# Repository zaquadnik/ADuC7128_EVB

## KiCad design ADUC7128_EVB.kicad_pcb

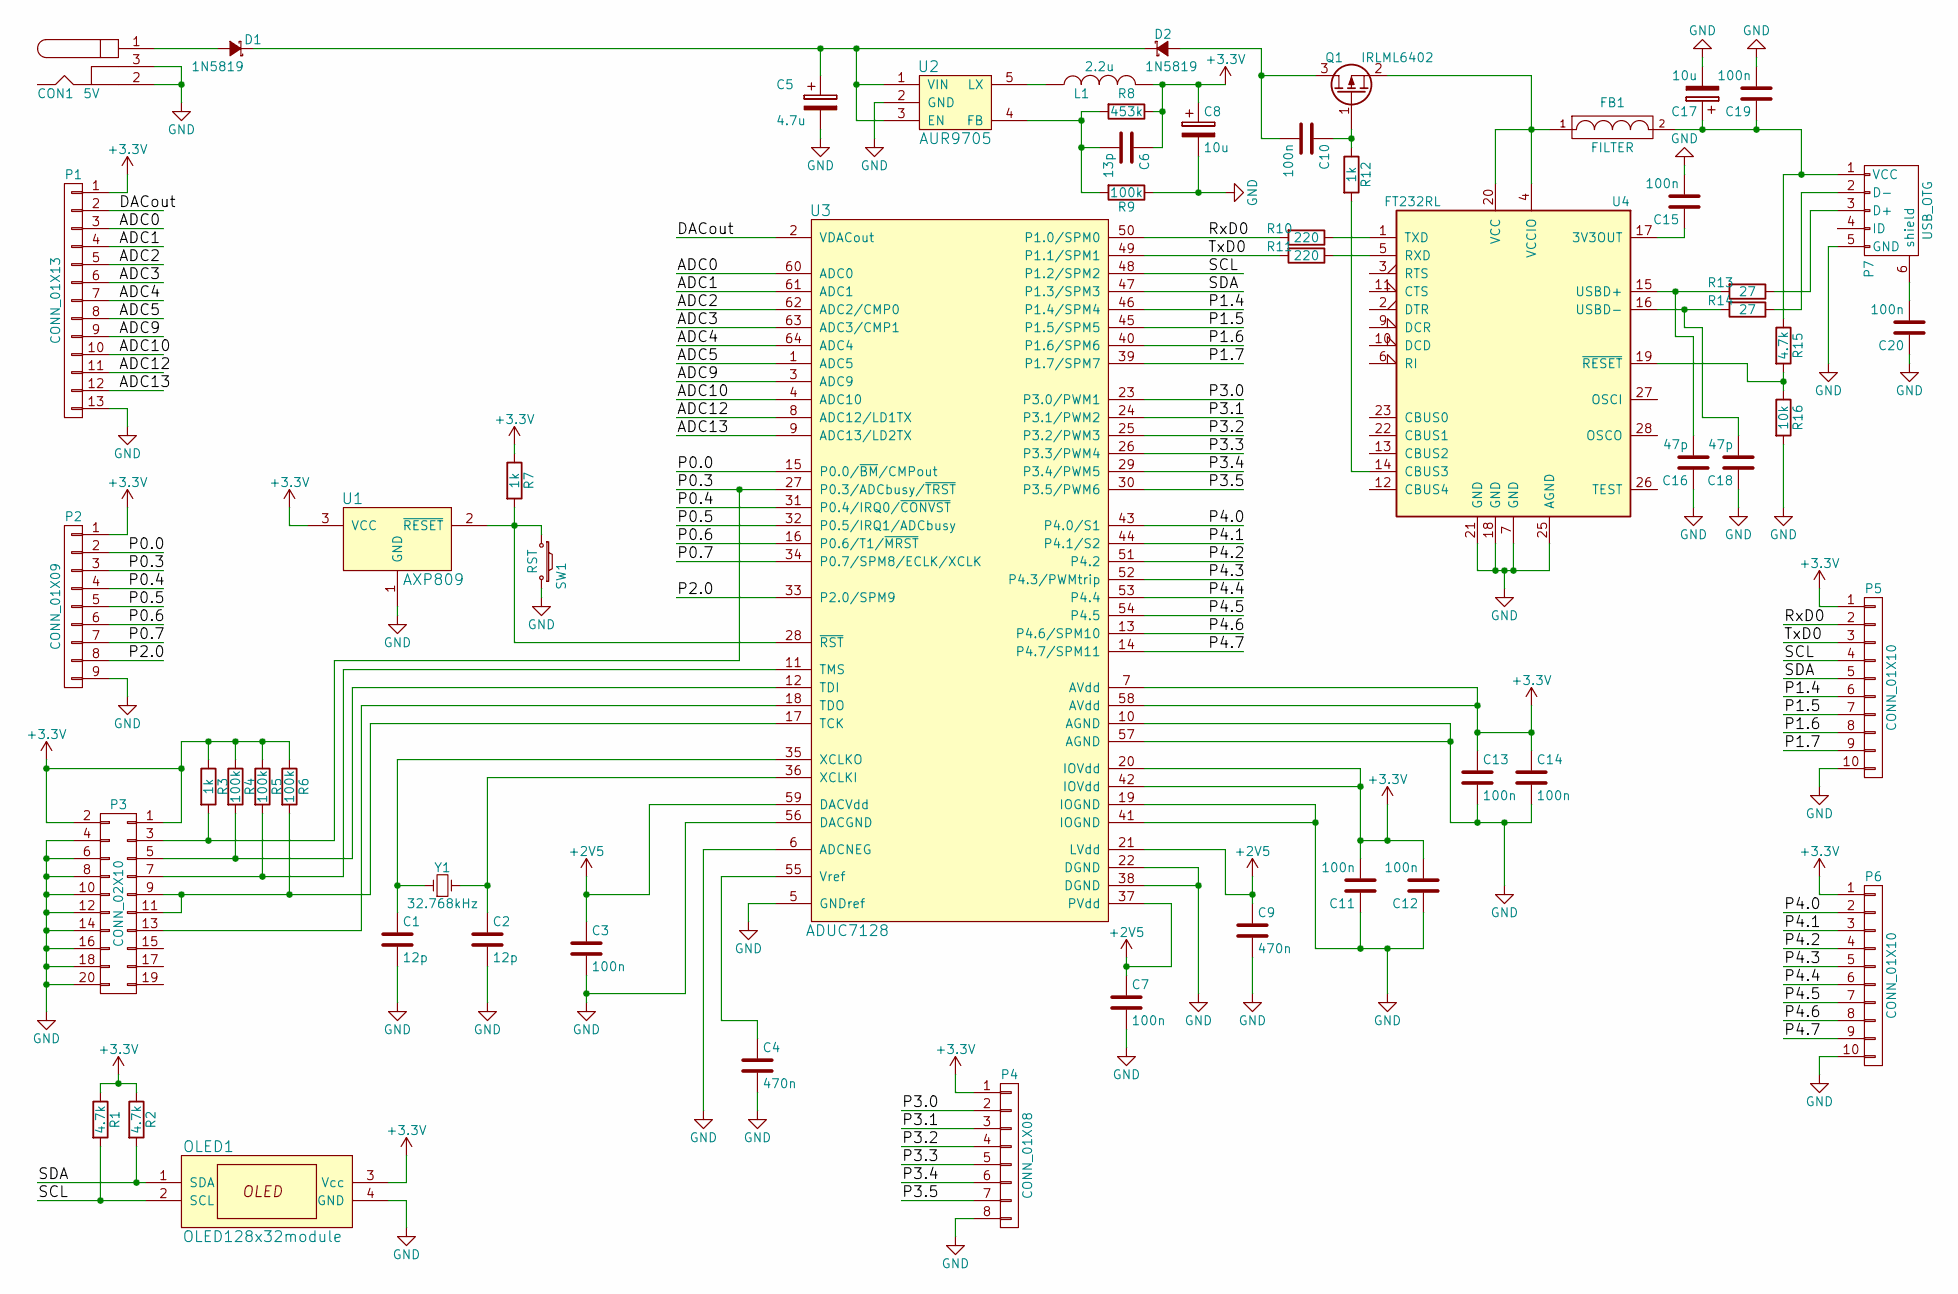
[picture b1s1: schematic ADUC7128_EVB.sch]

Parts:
C1, C2: 12p; C_0805_HandSoldering
C3, C7, C10, C11, C12, C13, C14, C15, C19, C20: 100n; C_0805_HandSoldering
C4, C9: 470n; C_0805_HandSoldering
C5: 4.7u; CP_Radial_D5.0mm_P2.00mm
C6: 13p; C_0805_HandSoldering
C8, C17: 10u; CP_Radial_D5.0mm_P2.50mm
C16, C18: 47p; C_0805_HandSoldering
CON1: 5V; BARREL_JACK
D1, D2: 1N5819; D_DO-41_SOD81_P7.62mm_Horizontal
FB1: FILTER; Choke_SMD_1206_Handsoldering
L1: 2.2u; Inductor_Taiyo-Yuden_NR-30xx_HandSoldering
OLED1: OLED128x32module; OLED_128x32_module
P1: CONN_01X13; Pin_Header_Straight_1x13_Pitch2.54mm
P2: CONN_01X09; Pin_Header_Straight_1x09_Pitch2.54mm
P3: CONN_02X10; Pin_Header_Straight_2x10_Pitch2.54mm
P4: CONN_01X08; Pin_Header_Straight_1x08_Pitch2.54mm
P5, P6: CONN_01X10; Pin_Header_Straight_1x10_Pitch2.54mm
P7: USB_OTG; USB_Mini-B
Q1: IRLML6402; SOT-23W_Handsoldering
R1, R2, R15: 4.7k; R_0603_HandSoldering
R3, R7, R12: 1k; R_0603_HandSoldering
R4, R5, R6, R9: 100k; R_0603_HandSoldering
R8: 453k; R_0603_HandSoldering
R10, R11: 220; R_0603_HandSoldering
R13, R14: 27; R_0603_HandSoldering
R16: 10k; R_0603_HandSoldering
SW1: RST; SW_PUSH_6mm
U1: AXP809; SC-59_Handsoldering
U2: AUR9705; TSOT-23-5_HandSoldering
U3: ADUC7128; QFP_64
U4: FT232RL; SSOP-28_5.3x10.2mm_Pitch0.65mm
Y1: 32.768kHz; Crystal_AT310_d3.0mm_l10.0mm_Vertical

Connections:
+2V5: C3.1, C7.1, C9.1, U3.21 (LVdd), U3.37 (PVdd), U3.59 (DACVdd)
+3V3: C6.1, C8.1, C11.2, C12.2, C13.1, C14.1, L1.2, OLED1.3 (Vcc), P1.1, P2.1, P3.1, P3.2, P4.1, P5.1, P6.1, R1.1, R2.1, R3.1, R4.1, R5.1, R6.1, R7.1, R8.1, U1.3 (VCC), U3.7 (AVdd), U3.20 (IOVdd), U3.42 (IOVdd), U3.58 (AVdd)
/ADC0: P1.3, U3.60 (ADC0)
/ADC1: P1.4, U3.61 (ADC1)
/ADC2: P1.5, U3.62 (ADC2/CMP0)
/ADC3: P1.6, U3.63 (ADC3/CMP1)
/ADC4: P1.7, U3.64 (ADC4)
/ADC5: P1.8, U3.1 (ADC5)
/ADC9: P1.9, U3.3 (ADC9)
/ADC10: P1.10, U3.4 (ADC10)
/ADC12: P1.11, U3.8 (ADC12/LD1TX)
/ADC13: P1.12, U3.9 (ADC13/LD2TX)
/DACout: P1.2, U3.2 (VDACout)
/P0.0: P2.2, U3.15 (P0.0/~BM~/CMPout)
/P0.3: P2.3, P3.3, R3.2, U3.27 (P0.3/ADCbusy/~TRST~)
/P0.4: P2.4, U3.31 (P0.4/IRQ0/~CONVST~)
/P0.5: P2.5, U3.32 (P0.5/IRQ1/ADCbusy)
/P0.6: P2.6, U3.16 (P0.6/T1/~MRST~)
/P0.7: P2.7, U3.34 (P0.7/SPM8/ECLK/XCLK)
/P1.4: P5.6, U3.46 (P1.4/SPM4)
/P1.5: P5.7, U3.45 (P1.5/SPM5)
/P1.6: P5.8, U3.40 (P1.6/SPM6)
/P1.7: P5.9, U3.39 (P1.7/SPM7)
/P2.0: P2.8, U3.33 (P2.0/SPM9)
/P3.0: P4.2, U3.23 (P3.0/PWM1)
/P3.1: P4.3, U3.24 (P3.1/PWM2)
/P3.2: P4.4, U3.25 (P3.2/PWM3)
/P3.3: P4.5, U3.26 (P3.3/PWM4)
/P3.4: P4.6, U3.29 (P3.4/PWM5)
/P3.5: P4.7, U3.30 (P3.5/PWM6)
/P4.0: P6.2, U3.43 (P4.0/S1)
/P4.1: P6.3, U3.44 (P4.1/S2)
/P4.2: P6.4, U3.51 (P4.2)
/P4.3: P6.5, U3.52 (P4.3/PWMtrip)
/P4.4: P6.6, U3.53 (P4.4)
/P4.5: P6.7, U3.54 (P4.5)
/P4.6: P6.8, U3.13 (P4.6/SPM10)
/P4.7: P6.9, U3.14 (P4.7/SPM11)
/RxD0: P5.2, R10.2, U3.50 (P1.0/SPM0)
/SCL: OLED1.2 (SCL), P5.4, R1.2, U3.48 (P1.2/SPM2)
/SDA: OLED1.1 (SDA), P5.5, R2.2, U3.47 (P1.3/SPM3)
/TxD0: P5.3, R11.2, U3.49 (P1.1/SPM1)
GND: C1.2, C2.2, C3.2, C4.2, C5.2, C7.2, C8.2, C9.2, C11.1, C12.1, C13.2, C14.2, C15.2, C16.1, C17.2, C18.1, C19.2, C20.1, CON1.2, CON1.3, OLED1.4 (GND), P1.13, P2.9, P3.4, P3.6, P3.8, P3.10, P3.12, P3.14, P3.16, P3.18, P3.20, P4.8, P5.10, P6.10, P7.5 (GND), R9.1, R16.2, SW1.2, U1.1 (GND), U2.2 (GND), U3.5 (GNDref), U3.6 (ADCNEG), U3.10 (AGND), U3.19 (IOGND), U3.22 (DGND), U3.38 (DGND), U3.41 (IOGND), U3.56 (DACGND), U3.57 (AGND), U4.7 (GND), U4.18 (GND), U4.21 (GND), U4.25 (AGND)
unnamed: C1.1, U3.35 (XCLKO), Y1.1
unnamed: C2.1, U3.36 (XCLKI), Y1.2
unnamed: C4.1, U3.55 (Vref)
unnamed: C5.1, D1.1 (K), D2.1 (K), U2.1 (VIN), U2.3 (EN)
unnamed: C6.2, R8.2, R9.2, U2.4 (FB)
unnamed: C10.1, Q1.1 (G), R12.1
unnamed: C10.2, D2.2 (A), Q1.3 (D)
unnamed: C15.1, U4.17 (3V3OUT)
unnamed: C16.2, R13.2, U4.15 (USBD+)
unnamed: C17.1, C19.1, FB1.2, P7.1 (VCC), R15.1
unnamed: C18.2, R14.2, U4.16 (USBD-)
unnamed: C20.2, P7.6 (shield)
unnamed: CON1.1, D1.2 (A)
unnamed: FB1.1, Q1.2 (S), U4.4 (VCCIO), U4.20 (VCC)
unnamed: L1.1, U2.5 (LX)
unnamed: P3.5, R4.2, U3.12 (TDI)
unnamed: P3.7, R5.2, U3.11 (TMS)
unnamed: P3.9, P3.11, R6.2, U3.17 (TCK)
unnamed: P3.13, U3.18 (TDO)
unnamed: P7.2 (D-), R14.1
unnamed: P7.3 (D+), R13.1
unnamed: R7.2, SW1.1, U1.2 (~RESET), U3.28 (~RST~)
unnamed: R10.1, U4.1 (TXD)
unnamed: R11.1, U4.5 (RXD)
unnamed: R12.2, U4.14 (CBUS3)
unnamed: R15.2, R16.1, U4.19 (~RESET~)

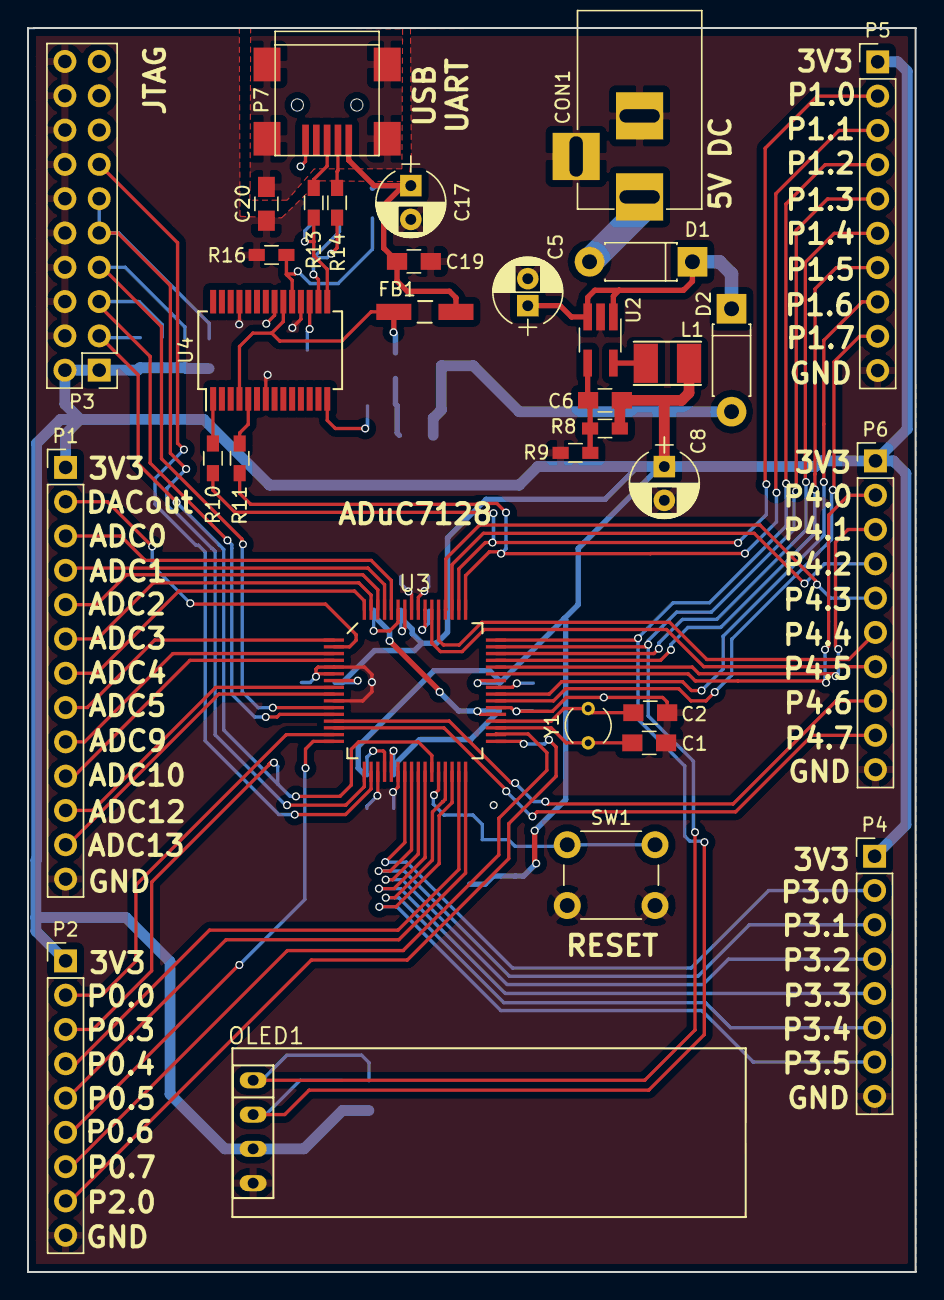
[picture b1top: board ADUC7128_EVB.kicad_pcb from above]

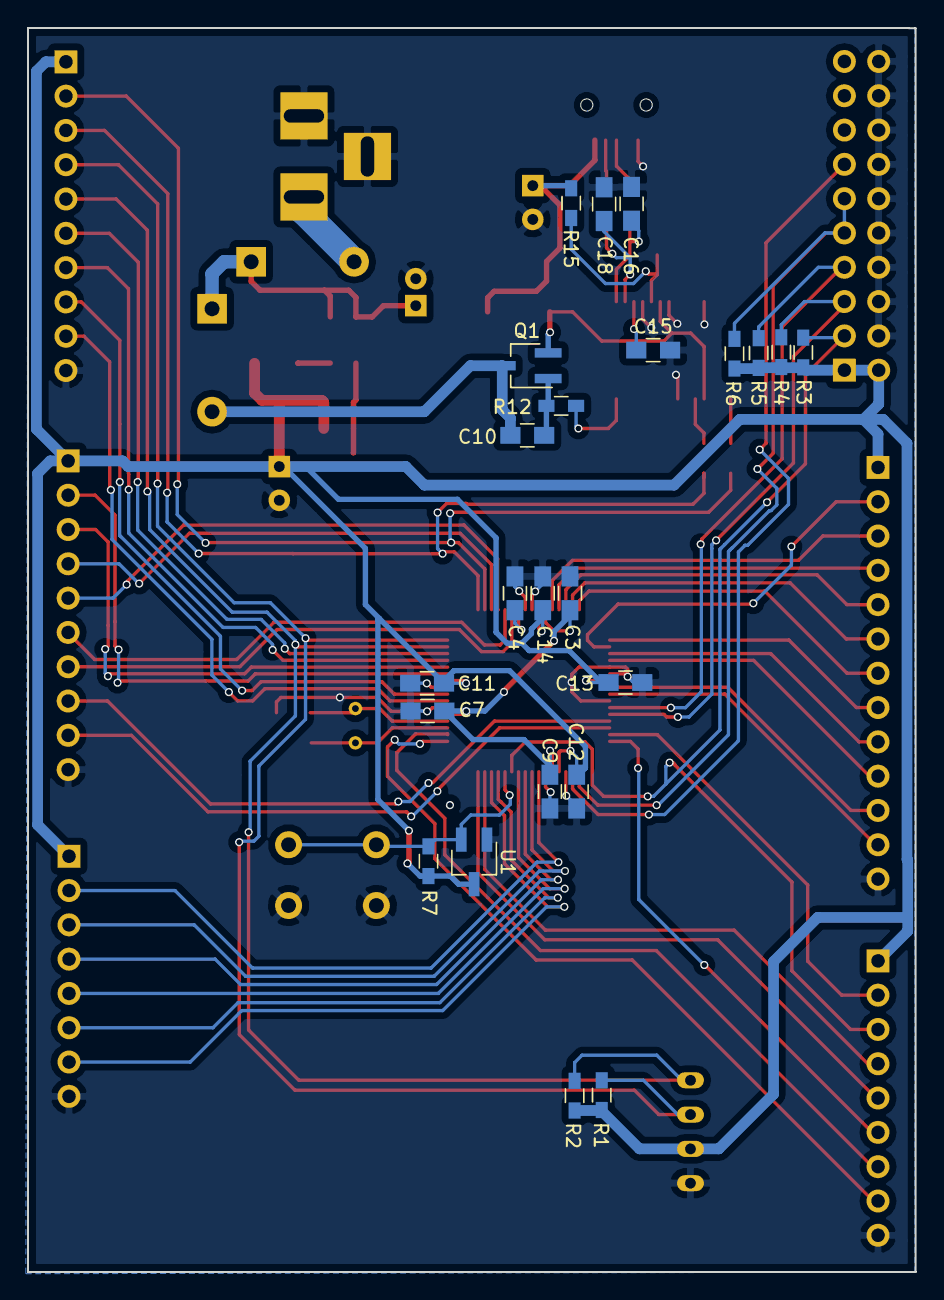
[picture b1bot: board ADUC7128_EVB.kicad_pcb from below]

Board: 2 copper layers, 65.7 x 92.1 mm, 56 parts (23 on the bottom side), 69 nets.
